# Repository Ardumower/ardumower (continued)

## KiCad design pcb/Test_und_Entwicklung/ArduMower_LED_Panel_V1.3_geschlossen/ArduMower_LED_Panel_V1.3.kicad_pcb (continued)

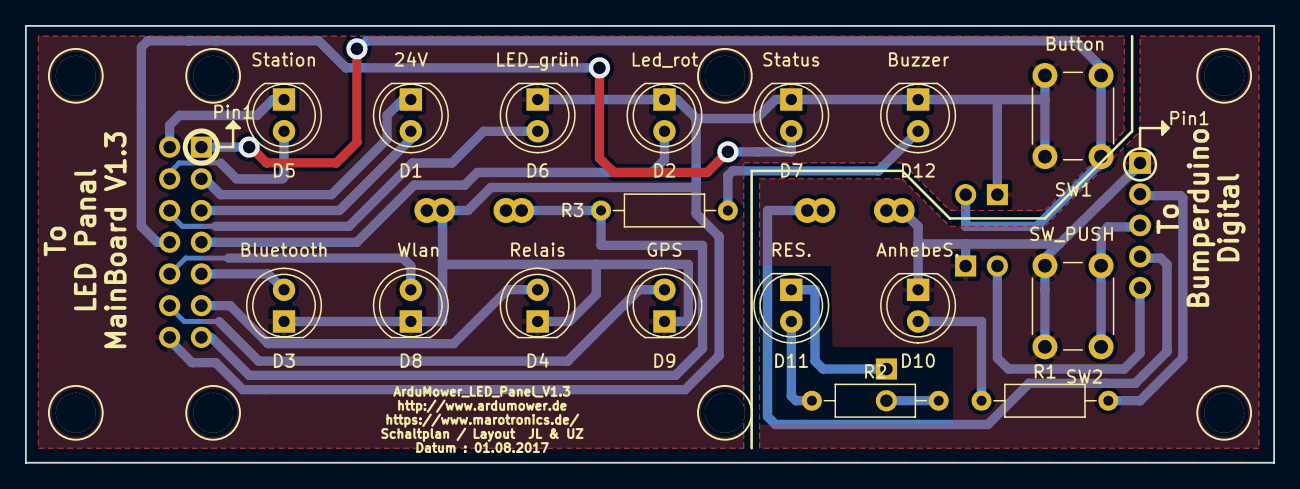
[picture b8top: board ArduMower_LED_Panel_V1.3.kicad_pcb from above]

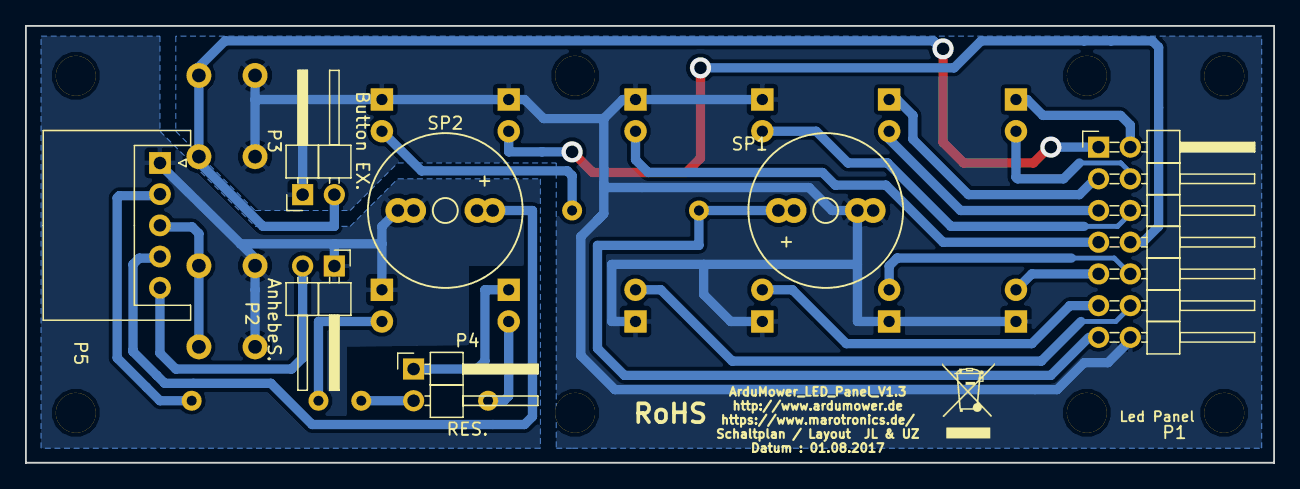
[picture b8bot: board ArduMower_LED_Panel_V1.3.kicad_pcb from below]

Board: 2 copper layers, 100.0 x 35.0 mm, 32 parts (7 on the bottom side), 24 nets.

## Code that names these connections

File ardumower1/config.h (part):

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// ------ configuration --------------------------------------------------
char configName[] = "kit10";
// ------ pins---------------------------------------
#define pinMotorEnable  37         // EN motors enable
#define pinMotorLeftPWM 5          // M1_IN1 left motor PWM pin
#define pinMotorLeftDir 31         // M1_IN2 left motor Dir pin
#define pinMotorLeftSense A1       // M1_FB  left motor current sense
#define pinMotorLeftFault 25       // M1_SF  left motor fault
                                                             
#define pinMotorRightPWM  3        // M2_IN1 right motor PWM pin
#define pinMotorRightDir 33        // M2_IN2 right motor Dir pin
#define pinMotorRightSense A0      // M2_FB  right motor current sense
#define pinMotorRightFault 27      // M2_SF  right motor fault
                                    
#define pinMotorMowPWM 2           // M1_IN1 mower motor PWM pin
#define pinMotorMowDir 29          // M1_IN2 mower motor Dir pin
#define pinMotorMowSense A3        // M1_FB  mower motor current sense
#define pinMotorMowFault 26        // M1_SF  mower motor fault
#define pinMotorMowEnable 28       // EN mower motor enable
#define pinMotorMowRpm 18
    
#define pinBumperLeft 39           // bumper pins
#define pinBumperRight 37
#define pinSonarCenterTrigger 24   // ultrasonic sensor pins
#define pinSonarCenterEcho 22
#define pinSonarRightTrigger 30    
#define pinSonarRightEcho 32
#define pinSonarLeftTrigger 34         
#define pinSonarLeftEcho 36
#define pinPerimeterRight A4       // perimeter
#define pinPerimeterLeft A5
//#define pinPerimeterMuxZ A6      // perimeter mux Z (only TC-G158 board)
#define pinLED 13                  // LED
#define pinBuzzer 53               // Buzzer
#define pinTilt 35                 // Tilt sensor (required for TC-G158 board)
#define pinButton 51               // digital ON/OFF button
#define pinBatteryVoltage A2       // battery voltage sensor
#define pinChargeVoltage A9        // charging voltage sensor
#define pinChargeCurrent A8        // charge current sensor
#define pinRemoteMow 12            // remote control mower motor
#define pinRemoteSteer 11          // remote control steering 
#define pinRemoteSpeed 10          // remote control speed
#define pinRemoteSwitch 52         // remote control switch
//#define pinMuxS0 28              // mux S0 (only TC-G158 board)
//#define pinMuxS1 26              // mux S1 (only TC-G158 board)
//#define pinMuxZ A7                 // mux Z (only TC-G158 board)
#define pinOdometryLeft A12         // left odometry sensor
#define pinOdometryLeft2 A13        // left odometry sensor (optional two-wire)
#define pinOdometryRight A15        // right odometry sensor
#define pinOdometryRight2 A14       // right odometry sensor (optional two-wire)
#define pinLawnFrontRecv 40        // lawn sensor front receive
#define pinLawnFrontSend 41        // lawn sensor front sender 
#define pinLawnBackRecv 42         // lawn sensor back receive
#define pinLawnBackSend 43         // lawn sensor back sender 
#define pinUserSwitch1 46          // user-defined switch 1
#define pinUserSwitch2 47          // user-defined switch 2
#define pinUserSwitch3 48          // user-defined switch 3
// compass/gyro/accel (I2C):   SCL ,  SDA 

// ------- baudrates---------------------------------
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ISR(PCINT0_vect)
{   
  unsigned long timeMicros = micros();
  boolean remoteSpeedState = digitalRead(pinRemoteSpeed);
  boolean remoteSteerState = digitalRead(pinRemoteSteer);
  boolean remoteMowState = digitalRead(pinRemoteMow);    
  boolean remoteSwitchState = digitalRead(pinRemoteSwitch);    
  setRemotePPMState(timeMicros, remoteSpeedState, remoteSteerState, remoteMowState, remoteSwitchState);    
}

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ISR(PCINT2_vect)
{   
  unsigned long timeMicros = micros();
  boolean odometryLeftState = digitalRead(pinOdometryLeft);
  boolean odometryLeftState2 = digitalRead(pinOdometryLeft2);
  boolean odometryRightState = digitalRead(pinOdometryRight);  
  boolean odometryRightState2 = digitalRead(pinOdometryRight2);  
  setOdometryState(timeMicros, odometryLeftState, odometryRightState, odometryLeftState2, odometryRightState2);
}

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  
  // LED, buzzer, battery
  pinMode(pinLED, OUTPUT);    
  pinMode(pinBuzzer, OUTPUT);    
  pinMode(pinBatteryVoltage, INPUT);        
  pinMode(pinChargeCurrent, INPUT);          
  pinMode(pinChargeVoltage, INPUT);            
  
  // left wheel motor
  pinMode(pinMotorEnable, OUTPUT);  
  digitalWrite(pinMotorEnable, HIGH);
  pinMode(pinMotorLeftPWM, OUTPUT);
  pinMode(pinMotorLeftDir, OUTPUT);   
  pinMode(pinMotorLeftSense, INPUT);     
  pinMode(pinMotorLeftFault, INPUT);    
  
  // right wheel motor
  pinMode(pinMotorRightPWM, OUTPUT);
  pinMode(pinMotorRightDir, OUTPUT); 
  pinMode(pinMotorRightSense, INPUT);       
  pinMode(pinMotorRightFault, INPUT);  
  
  // mower motor
  pinMode(pinMotorMowDir, OUTPUT); 
  pinMode(pinMotorMowPWM, OUTPUT);     
  pinMode(pinMotorMowSense, INPUT);     
  pinMode(pinMotorMowRpm, INPUT);     
    
  // lawn sensor
  pinMode(pinLawnBackRecv, INPUT);
  pinMode(pinLawnBackSend, OUTPUT);
  pinMode(pinLawnFrontRecv, INPUT);
  pinMode(pinLawnFrontSend, OUTPUT);  
  
  // perimeter
  pinMode(pinPerimeterRight, INPUT);    
  pinMode(pinPerimeterLeft, INPUT);        
  
  // button
  pinMode(pinButton, INPUT);
  pinMode(pinButton, INPUT_PULLUP);

  // bumpers  
  pinMode(pinBumperLeft, INPUT); 
  pinMode(pinBumperLeft, INPUT_PULLUP);
  pinMode(pinBumperRight, INPUT);     
  pinMode(pinBumperRight, INPUT_PULLUP);
  
  // sonar
  pinMode(pinSonarCenterTrigger, OUTPUT); 
  pinMode(pinSonarCenterEcho, INPUT); 
  pinMode(pinSonarLeftTrigger, OUTPUT); 
  pinMode(pinSonarLeftEcho, INPUT); 
  pinMode(pinSonarRightTrigger, OUTPUT); 
  pinMode(pinSonarRightEcho, INPUT); 
      
  // mower motor speed sensor interrupt
  attachInterrupt(5, rpm_interrupt, CHANGE);
  
  // R/C
  pinMode(pinRemoteMow, INPUT);
  pinMode(pinRemoteSteer, INPUT);
  pinMode(pinRemoteSpeed, INPUT); 
  pinMode(pinRemoteSwitch, INPUT);       
  #ifdef __AVR__
    PCICR |= (1<<PCIE0);
    PCMSK0 |= (1<<PCINT4);
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  #endif   
  
  // odometry
  pinMode(pinOdometryLeft, INPUT_PULLUP);  
  pinMode(pinOdometryLeft2, INPUT_PULLUP);    
  pinMode(pinOdometryRight, INPUT_PULLUP);
  pinMode(pinOdometryRight2, INPUT_PULLUP);  
  #ifdef __AVR__  
    PCICR |= (1<<PCIE2);
    PCMSK2 |= (1<<PCINT20);
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  #endif
  
  // user switches
  pinMode(pinUserSwitch1, OUTPUT);
  pinMode(pinUserSwitch2, OUTPUT);
  pinMode(pinUserSwitch3, OUTPUT);   
  
  // ADC
  ADCMan.init();
  ADCMan.setCapture(pinMotorMowSense, 1, 1);
  ADCMan.setCapture(pinMotorLeftSense, 1, 1);
  ADCMan.setCapture(pinMotorRightSense, 1, 1);
  ADCMan.setCapture(pinBatteryVoltage, 1, 0);
  Perimeter.setPins(pinPerimeterLeft, pinPerimeterRight);      
}

void checkMotorFault(){
  if ( (digitalRead(pinMotorLeftFault)==LOW) || (digitalRead(pinMotorRightFault)==LOW) ){
    digitalWrite(pinMotorEnable, LOW);
    digitalWrite(pinMotorEnable, HIGH);
  }
}

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  
  switch (type) {
// motors------------------------------------------------------------------------------------------------
    case SEN_MOTOR_MOW: return ADCMan.read(pinMotorMowSense); break;
    case SEN_MOTOR_RIGHT: checkMotorFault(); return ADCMan.read(pinMotorRightSense); break;
    case SEN_MOTOR_LEFT:  checkMotorFault(); return ADCMan.read(pinMotorLeftSense); break;
    //case SEN_MOTOR_MOW_RPM: break; // not used - rpm is upated via interrupt

// perimeter----------------------------------------------------------------------------------------------
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    //case SEN_PERIM_RIGHT: return Perimeter.getMagnitude(1); break;
    
// battery------------------------------------------------------------------------------------------------
    case SEN_BAT_VOLTAGE: return ADCMan.read(pinBatteryVoltage); break;
    //case SEN_CHG_VOLTAGE: return((int)(((double)analogRead(pinChargeVoltage)) * batFactor)); break;
    //case SEN_CHG_CURRENT: return((int)(((double)analogRead(pinChargeCurrent)-chgSenseZero) * chgFactor)); break;
    
// buttons------------------------------------------------------------------------------------------------
    case SEN_BUTTON: return(digitalRead(pinButton)); break; 
    
//bumper----------------------------------------------------------------------------------------------------
    case SEN_BUMPER_RIGHT: return(digitalRead(pinBumperRight)); break;
    case SEN_BUMPER_LEFT: return(digitalRead(pinBumperLeft)); break;      
    
// sonar---------------------------------------------------------------------------------------------------
    //case SEN_SONAR_CENTER: return(readURM37(pinSonarCenterTrigger, pinSonarCenterEcho)); break;  
    //case SEN_SONAR_CENTER: return(readHCSR04(pinSonarCenterTrigger, pinSonarCenterEcho)); break;  
    case SEN_SONAR_LEFT: return(readHCSR04(pinSonarLeftTrigger, pinSonarLeftEcho)); break; 
    case SEN_SONAR_RIGHT: return(readHCSR04(pinSonarRightTrigger, pinSonarRightEcho)); break;    
    //case SEN_LAWN_FRONT: return(measureLawnCapacity(pinLawnFrontSend, pinLawnFrontRecv)); break;    
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
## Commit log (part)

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2017-04-22 ultrasonic test: optimized for 3 sensors and interrupt
2017-04-26 new gerber: RS-274-X
2017-05-09 megashield_svn_1.3_geoeffnet
    megashield_svn_1.3_geoeffnet
    neue PlatinenAnsicht erstellt für die Bestückung in China
    Bilder Platinenansicht für die Bestückung in China hinzugefügt
    Fehler behoben
    an den Dioden D2 und D7 in der 3D Ansicht die Ansicht vergrößert und die
    Diode um 180Grad gedreht.
2017-05-11 megashield_svn_1.3_geoeffnet
    megashield_svn_1.3_geoeffnet
    Beschriftung PIN1 ICs hinzugefügt auf User Layer
2017-05-17 detection for new HC-06 Bluetoth modules
2017-05-19 update FSM
2017-05-20 sonar test adjusted for PCB
2017-05-23 sonar test tidy up
2017-05-29 megashield_svn_1.3_geoeffnet
    Das Projekt umbenannt von
    megashield_svn_1.3_geoeffnet
    in
    megashield_svn_1.3_geschlossen
    und in den Ordner Produzierte_Platinen verschoben
2017-06-04 Very smooth perimeter tracking
2017-06-05 Spaces removed
2017-06-05 Revert "get PerimeterMax while STATE_PERI_FIND only"
    This reverts commit 548941f53de800ab5181d67ceb7eadff1bf19eac.
2017-06-05 this is too much...
2017-06-06 Due: pin debounce
2017-06-06 PCB 1.3 : odometry interrupt - untested
2017-06-07 original default battery values
2017-06-08 pcb1.3 schematics
2017-06-15 charging current low pass filter
2017-06-17 mini: correct battery values
2017-06-17 PCB 1.3 : startChargingIfBelow must be 32v
2017-06-17 default sonar values
2017-06-18 remove Programmiertools
2017-06-19 processing_remote: add win32 binary
2017-06-20 compilation fix
2017-06-23 perimeter PID change
2017-06-26 Änderungen Perimeterverfolgung und neue Bumper Zustände / Changes perimeter tracking and new bumper states
    Perimeterverfolgung von Holoratte geprüft und Ok.
    Neue Bumper Zustände geprüft und berichtigt OK
    kleine Änderung Copyright
    Perimeter tracking of Holoratte checked and Ok.
    New bumper states checked and corrected OK
    Small change copyright
2017-06-27 new opton useChooseDevice
2017-07-01 new error: ERR_CPU_SPEED (indicating I2C cable problems etc.)
2017-07-04 new error: ERR_CPU_SLOW - better implementation
2017-07-09 ArduMower_LED_Panel_V1.3_geoeffnet hinzugefügt
    ArduMower_LED_Panel_V1.3_geoeffnet hinzugefügt
2017-07-13 Changes to use L298N motor drivers
    I use L298N drivers, so I changed the call s of ACT_MOTOR_* to become more general
2017-07-19 Trigger value changed
    Wert für Empfindlichkeit geändet
    Value changed for sensitivity
2017-07-23 more detailed i2c error output
2017-07-23 battery events: show voltages in console
2017-07-24 ArduMower_LED_Panel_V1.3_geoeffnet
    ArduMower_LED_Panel_V1.3_geoeffnet
    Klemme Bezeichnung J1 nach P5 umgeändert
    Klemme P5 Footprint geändert
    -war falsch - Pin1 war Pin5, Pin5 war Pin1 usw....
2017-07-28 Ardumower
    Fehler bei der Verwendung von den 1.3 Board behoben.
    Die Spannungsanzeige des Akkus war zu niedig weil der Spannungsabfall
    der Diode D9 auf den Board V1.3 nicht berücksichtigt wurde. Eine
    Variable D9 wurde hinzugefügt für den Spannungsabfall
2017-07-31 ArduBumperPerimeterDuino_V3.00.ABPD_geschlossen
    ArduBumperPerimeterDuino_V3.00.ABPD_geschlossen
    Symbole in der 3d Ansicht berichtigt wegen neuer KIcad Symbol Ansichten
    RoHS Symbol und Mülleimer Symbol hinzugefügt
    ------------------------------------------------------------------------
    Es wurden keine Änderungen am Schaltplan,Layout oder dergleichen
    vorgenommen
2017-08-03 add pinman comment
2017-08-13 ArduMower_RaspberryPi_Power_Switch_V1.0_geoeffnet
    ArduMower_RaspberryPi_Power_Switch_V1.0_geoeffnet
    RoHos Beschriftung und Mülleimer hinzugefügt
2017-08-16 smaller changes
2017-09-13 Bumper Hit when reaching charging station
    Tianchen charge pins are attached on bumper. So in most cases, bumper gets triggered when mower hits station.
    To avoid reverse and roll (resulting in never find back to station), first check if charge pins are connected
2017-12-05 Added FIle RMCS.H, no code
2018-01-10 Perimeter Sender V3.0
    Perimeter Sender V3.0 + mit automatischer Leistungsregelung
    + evl 2 messoptionen zur überprüfung und fehlersuche der Messschleife
2018-01-24 KICAD
2018-03-14 megashield_svn_1.3_geschlossen
    megashield_svn_1.3_geschlossen
    Schönheitsfehler in Plan verbessert
    Bei dem globalen Maker "pinRemoteSwitch" war in den Schaltpanseite bei
    dem Due die Signalrichtung falsch eingezeichnet.
    Signalrichtung wurde umgeändert
    Die Änderung hat kein Einfluß auf die Funktion der Schaltung
2018-03-28 INA169_StromSensor_V1.1_geschlossen
    INA169_StromSensor_V1.1_geschlossen
    Projekt geschlossen und in den Ordner Produzierte_Platinen verschoben
2018-04-14 Komentare eingefügt / Comments inserted
2018-04-16 removed settings output
2018-04-16 added i2c scanner, improved menu structure
2018-04-16 mega: proper i2c warning
2018-04-19 ignore sensors (bumper, freewheel ,perimeter, bumper) when not usee
2018-04-19 allow broken AT24C32 to start
2018-04-20 new develop version
2018-05-13 import note for factory settings
2018-05-17 ros: better serial port handling
2018-05-19 ROS: better interface params
2018-05-24 Charge detection
    Correction for charge detection
2018-05-24 ros: moved variables into robot.h
2018-05-25 introduced ardumower ros package
2018-05-27 odometry calculation bugfix
2018-06-08 RMCS sommands and new Events
    Added RMCS commands and Events
2018-06-12 Added RMCS Trigger parameter to methods
    Changed the RMCS send event methods so they include trigger parameter
2018-06-22 RMCS bugfixes
2018-07-08 GPS added to RMCS messages
    RMCS message added for GPS data (lat/lon)
2018-07-11 small bug fixes for RMCS messages
2018-11-09 megashield_svn_1.3_geschlossen
    megashield_svn_1.3_geschlossen
    Neue Pfade für die 3D Ansicht berichtigt.
    Die 3D Ansichten wurden von Kicad unbenannt
2019-04-12 sender_v3.0_geoeffnet
    sender_v3.0_geoeffnet Prototypplatine erstellt
2020-03-30 Change in software reset for Due
    According to the datasheet, p.236, the dword to reset proc, periph and extern RST to low is 0xA500000D (bit 0 =1, bit 2 = 1, bit 3 = 1)
2020-04-27 https://forum.ardumower.de/threads/perimeteroutreversetime.23723/
2020-05-14 Robot class: Use Initializer lists
2020-05-14 Cleanup PID
    - Initializer lists
    - AStyle
2020-05-24 Try reset I2C /w IMU in case of read error
2020-05-25 avoid dividing by zero
2020-06-01 Turns in floats and 90 IMU degrees
2020-06-04 Revert "with odometry, set the direction to current yaw"
    This reverts commit 6063aeee2ff0728a06a6f3beab9da904786c050d.
2020-06-11 make sure we deal with at least floats
2020-06-23 Choose random direction for turns with MOW_RANDOM
2020-07-05 megashield_svn_1.4_geoeffnet
    megashield_svn_1.4_geoeffnet
    Fehlerbehebung:
    An den Arduino Mega die Verdrahtung von Pin 14 und 15 getauscht damit RX
    un TX vom GPS Anschluss stimmt.
    _____________________________________________________________________________________________________________________
2020-09-21 add sdcard test
2020-11-01 first write
    Never tested in real condition
2020-12-14 add IMU MPU9250/MPU9255
2020-12-14 push date to 2020 in pfod
2020-12-17 megashield_svn_1.4_geoeffnet
    megashield_svn_1.4_geoeffnet gelöscht
2020-12-17 megashield_svn_1.4_geoeffnet
    megashield_svn_1.4_geoeffnet
    3 R47 und R48 mit 10K bestueckt
2020-12-17 megashield_svn_1.4_geoeffnet
    megashield_svn_1.4_geoeffnet
    6 INA169 geaendert auf direkte Platinenbestückung
2020-12-17 megashield_svn_1.4_geoeffnet
    megashield_svn_1.4_geoeffnet
    9 Fehler beim Messen der Akkuspannung behoben
2020-12-17 megashield_svn_1.4_geoeffnet
    megashield_svn_1.4_geoeffnet
    12 Bauteile Links hinzugefügt
2020-12-17 megashield_svn_1.4_geoeffnet
    megashield_svn_1.4_geoeffnet
    15 3D Ansichten aktualesiert
2021-01-01 megashield_svn_1.4_geoeffnet
    megashield_svn_1.4_geoeffnet
    18 Notaus P49 Leiterbahnbrücke hinzugefügt und unbenannt in MotorStop
2021-01-02 megashield_svn_1.4_geoeffnet
    21 Verdrahtungfehler bei Levelshifter behoben
    VCCA auf den Pegel Jumper gelegt für Wlan, BT
    und Gps Glättungskondensatoren hinzugefügt
2021-01-04 megashield_svn_1.4_geoeffnet
    megashield_svn_1.4_geoeffnet
    24 INA Neu verdrahtet und Widerstandswerte von den INA ausgetauscht
    Berechnung hinzugefügt
2021-01-07 megashield_svn_1.4_geoeffnet
    megashield_svn_1.4_geoeffnet
    27 SchaltplanSymbol der Diode DKE1 und DKE2 auf eine BIdirektinal Diode abgeändert
2021-01-09 megashield_svn_1.4_geoeffnet
    megashield_svn_1.4_geoeffnet
    31 U6,U7 JLCCPCB Nummer ergänzt
2021-01-09 megashield_svn_1.4_geoeffnet
    megashield_svn_1.4_geoeffnet
    37 D2,D7 Bauform auf SMA geändert +neue JLCPCB Nummer
2021-01-09 megashield_svn_1.4_geoeffnet
    megashield_svn_1.4_geoeffnet
    40 D17-23 Footprint auf 0805 umgeändert + neue JLCPCB Nummer
2021-01-14 megashield_svn_1.4_geoeffnet
    megashield_svn_1.4_geoeffnet
    43 neue JLCPCB Nummer Für CC1,CC2,CC3,EF1,U4,U9,U12,U6,U7,PC1-PC7
2021-01-14 megashield_svn_1.4_geoeffnet
    megashield_svn_1.4_geoeffnet
    46 Nullpunkt auf Platine umgesetzt
2021-01-18 megashield_svn_1.4_geoeffnet
    megashield_svn_1.4_geoeffnet
    49 JLCPCB Nummern geändert
2021-01-20 megashield_svn_1.4_geoeffnet
    megashield_svn_1.4_geoeffnet
    52 Gerberfiles und Schaltplan hinzugefügt
2021-02-21 rename MPU to MPU92xx to resolved conflict with Arduino Due
2021-03-05 Workaround to work under Arduino 1.8
2021-03-16 Console: show softwareversion in setup menu d
2021-03-19 new dev version 1.0a11-dev
2021-03-19 fix compiler warning RunningMedian
2021-03-27 pull request change last Changed int's to float's in pid.cpp
2021-05-05 INA169_StromSensor_V1.2_geoeffnet
    INA169_StromSensor_V1.2_geoeffnet
    Gerber Files hinzugefügt
2021-05-17 INA169_StromSensor_V1.2_geschlossen
    INA169_StromSensor_V1.2_geoeffnet unbenannt in INA169_StromSensor_V1.2_geschlossen
    Projekt von den Ordner Test und Entwicklung in den Ordner produzierte Platinen verschoben.
    Überflüssige entpackte Dateien gelöscht
2021-05-27 megashield_svn_1.4_Prototyp_Intern_geschlossen
    megashield_svn_1.4_Prototyp_Intern_geschlossen
    3D Kicad Symbolpfade angepasst
    Anmerkungen in Schaltplan zu den Änderungen der 1.4 Platine entfernt
    Schaltplan als PDF erstellt
    Datei Leichen in Archiv verschoben
    Unterordner für Datenblättererstellt
2021-05-27 megashield_svn_1.4_geschlossen
    megashield_svn_1.4_geschlossen
    aus dem Ordner "Test_und_Entwicklung"
    in den Ordner "Produzierte_Platinen"
    verschoben
2021-06-02 megashield_svn_1.4_geschlossen
    megashield_svn_1.4_geschlossen
    Datei Leichen entfernt
2021-06-08 Ardumower Platine V1.4 Aufbauanleitung
    Ardumower Platine V1.4 Aufbauanleitung aktuallesiert
2021-07-14 Upload BL Driver Layout
2021-07-19 gitignore changes
2021-08-02 Ardumower Platine V1.4 Aufbauanleitung
    Ardumower Platine V1.4 Aufbauanleitung
    Ergänzt und aktualisiert.
    - Kapitel 30.1 Die automatische Abschaltung
    - Kapitel 32.3. Der Betriebs Taster oder auch Button
    - Hinweis wegen 2 Buzzer Anschlüssen ergänzt
2021-10-21 adjusted rc test code
2021-12-20 Update DRV8308_SPI_Nano.ino
    ?- Print changed
2022-01-30 für Kicad 6.99 geänderte Library Footprint und 3D Grafiken angepasst
    für Kicad 6.99 geänderte Library Footprint und 3D Grafiken angepasst
2022-03-14 Ardumower Platine V1.4 Aufbauanleitung
    Ardumower Platine V1.4 Aufbauanleitung auf Version V1.4 r10
    Ergänzt und aktualisiert. - durch Willy
    - Ergänzt Kapitel 32. IMU anschließen (Seite 49)
    - Ergänzt Kapitel 33. HTU21D Temperatursensor anschließen (Seite 50)
2022-05-20 TB9051FTG_Motortreiber_V1.0_geoeffnet
    TB9051FTG_Motortreiber_V1.0_geoeffnet
2022-06-13 TB9051FTG_Motortreiber_V1.0_geoeffnet
    TB9051FTG_Motortreiber_V1.0_geoeffnet
    Falscher Widerstandswert R11 von1k auf 220 Ohm korrigiert
